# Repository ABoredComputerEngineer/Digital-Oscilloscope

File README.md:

# How to Run

* Requires `make`, `avr-gcc` and `avr-dude` for generating and flashing hex files
* Requires `numpy` and `matplotlib` for generating plots

### To Compile:
From project directory ( in the command line ), run:
```
make 
```
### To Flash:
* Make sure that the correct Arduino COM port is selected in the `Makefile`
From project directory ( in the command line ), run:
```
make flash
```

### To Generate Data for plot:
Once the program has been flashed and running, select the correct COM port for the USB-TTL
and run
```
python src/test.py > src/data
```
Hit `Ctrl-C` to stop execution once you think you have enough data and then run
```
python src/plot.py
```

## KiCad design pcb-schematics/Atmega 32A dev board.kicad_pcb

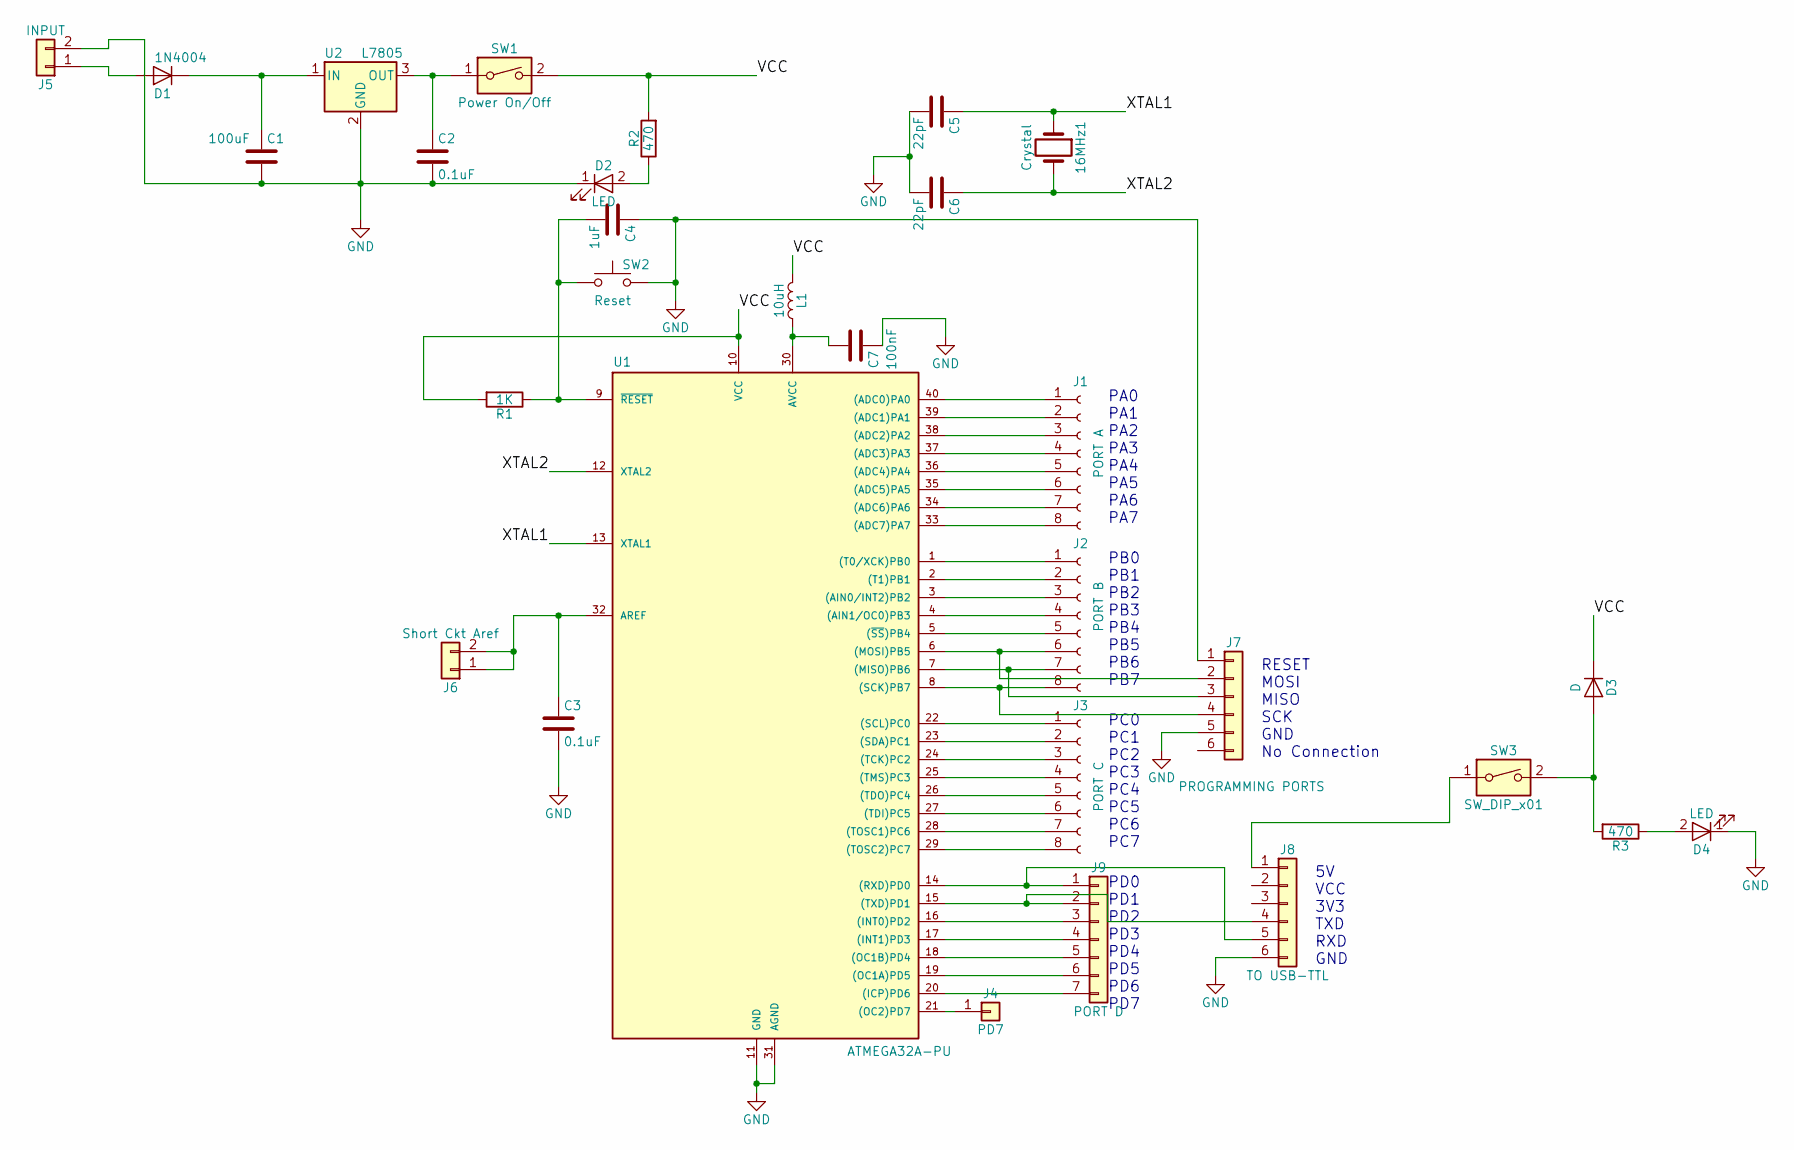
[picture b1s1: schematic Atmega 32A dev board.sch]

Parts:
16MHz1: Crystal
C1: 100uF; Capacitor_100uF
C2, C3: 0.1uF; Capacitor_Disc_Small
C4: 1uF; Capacitor_Disc_Small
C5, C6: 22pF; Capacitor_Disc_Medium
C7: 100nF; Capacitor_Disc_Small
D1: 1N4004; Diode_Medium
D2, D4: LED; LED_D3.0mm
D3: D; Diode_Medium
J1: PORT A; Socket_Strip_Straight_1x08_Pitch2.54mm
J2: PORT B; Socket_Strip_Straight_1x08_Pitch2.54mm
J3: PORT C; Socket_Strip_Straight_1x08_Pitch2.54mm
J4: PD7; Socket_Strip_Straight_1x01_Pitch2.54mm
J5: INPUT; Connector_Bornier_2
J6: Short Ckt Aref; Pin_Header_Straight_1x02_Pitch2.54mm
J7: PROGRAMMING PORTS; Socket_Strip_Straight_1x06_Pitch2.54mm
J8: TO USB-TTL; Socket_Strip_Straight_1x06_Pitch2.54mm
J9: PORT D; Socket_Strip_Straight_1x07_Pitch2.54mm
L1: 10uH; Resistor_small
R1: 1K; Resistor_small
R2, R3: 470; Resistor_small
SW1: Power On/Off; DIP_Switch
SW2: Reset; Push_Button
SW3: SW_DIP_x01; DIP_Switch
U1: ATMEGA32A-PU; DIP-40
U2: L7805; Voltage_Regulators

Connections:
/VCC: D3.1 (K), L1.2, R1.2, R2.2, SW1.2, U1.10 (VCC)
/XTAL1: 16MHz1.1, C5.1, U1.13 (XTAL1)
/XTAL2: 16MHz1.2, C6.1, U1.12 (XTAL2)
GND: C1.2, C2.2, C3.2, C4.1, C5.2, C6.2, C7.1, D2.1 (K), D4.1 (K), J5.2, J7.1, J7.5, J8.6, SW2.2, U1.11 (GND), U1.31 (AGND), U2.2 (GND)
unnamed: C1.1, D1.1 (K), U2.1 (IN)
unnamed: C2.1, SW1.1, U2.3 (OUT)
unnamed: C3.1, J6.1, J6.2, U1.32 (AREF)
unnamed: C4.2, R1.1, SW2.1, U1.9 (~RESET)
unnamed: C7.2, L1.1, U1.30 (AVCC)
unnamed: D1.2 (A), J5.1
unnamed: D2.2 (A), R2.1
unnamed: D3.2 (A), R3.2, SW3.2
unnamed: D4.2 (A), R3.1
unnamed: J1.1, U1.40 ((ADC0)PA0)
unnamed: J1.2, U1.39 ((ADC1)PA1)
unnamed: J1.3, U1.38 ((ADC2)PA2)
unnamed: J1.4, U1.37 ((ADC3)PA3)
unnamed: J1.5, U1.36 ((ADC4)PA4)
unnamed: J1.6, U1.35 ((ADC5)PA5)
unnamed: J1.7, U1.34 ((ADC6)PA6)
unnamed: J1.8, U1.33 ((ADC7)PA7)
unnamed: J2.1, U1.1 ((T0/XCK)PB0)
unnamed: J2.2, U1.2 ((T1)PB1)
unnamed: J2.3, U1.3 ((AIN0/INT2)PB2)
unnamed: J2.4, U1.4 ((AIN1/OC0)PB3)
unnamed: J2.5, U1.5 ((~SS~)PB4)
unnamed: J2.6, J7.2, U1.6 ((MOSI)PB5)
unnamed: J2.7, J7.3, U1.7 ((MISO)PB6)
unnamed: J2.8, J7.4, U1.8 ((SCK)PB7)
unnamed: J3.1, U1.22 ((SCL)PC0)
unnamed: J3.2, U1.23 ((SDA)PC1)
unnamed: J3.3, U1.24 ((TCK)PC2)
unnamed: J3.4, U1.25 ((TMS)PC3)
unnamed: J3.5, U1.26 ((TDO)PC4)
unnamed: J3.6, U1.27 ((TDI)PC5)
unnamed: J3.7, U1.28 ((TOSC1)PC6)
unnamed: J3.8, U1.29 ((TOSC2)PC7)
unnamed: J4.1, U1.21 ((OC2)PD7)
unnamed: J8.1, SW3.1
unnamed: J8.4, J9.2, U1.15 ((TXD)PD1)
unnamed: J8.5, J9.1, U1.14 ((RXD)PD0)
unnamed: J9.3, U1.16 ((INT0)PD2)
unnamed: J9.4, U1.17 ((INT1)PD3)
unnamed: J9.5, U1.18 ((OC1B)PD4)
unnamed: J9.6, U1.19 ((OC1A)PD5)
unnamed: J9.7, U1.20 ((ICP)PD6)

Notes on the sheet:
RESET MOSI MISO SCK GND No Connection
5V VCC 3V3 TXD RXD GND
PA0 PA1 PA2 PA3 PA4 PA5 PA6 PA7
PB0 PB1 PB2 PB3 PB4 PB5 PB6 PB7
PC0 PC1 PC2 PC3 PC4 PC5 PC6 PC7
PD0 PD1 PD2 PD3 PD4 PD5 PD6 PD7

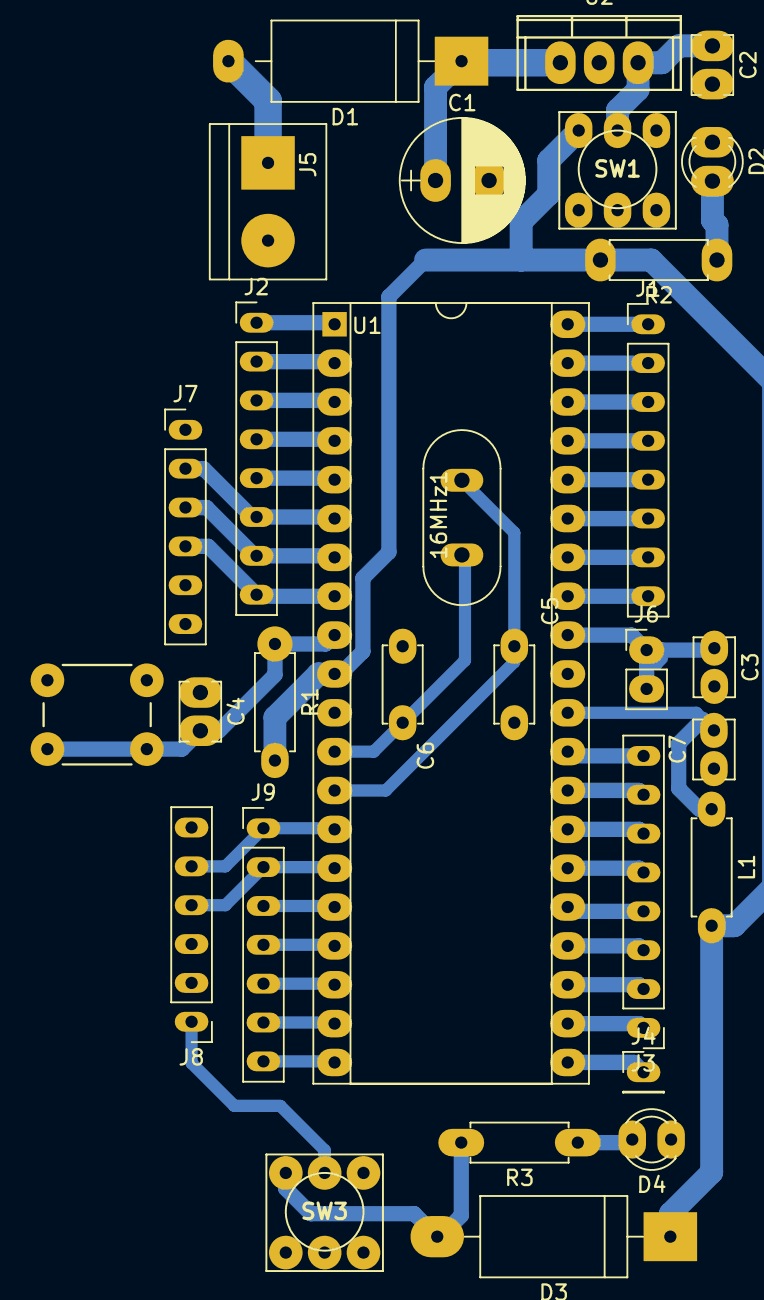
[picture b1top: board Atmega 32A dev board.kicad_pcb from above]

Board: 2 copper layers, 30 parts (0 on the bottom side), 46 nets.

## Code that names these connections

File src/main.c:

#define CLOCK_FREQUENCY
#define SANITY_CHECK 1

#ifndef F_CPU
  #define F_CPU 1000000
#endif

#include <avr/io.h>
#include <util/delay.h>
#include "setbaud.h"
#include <avr/interrupt.h>
#include <stdbool.h>

typedef unsigned int uint;
typedef uint16_t u16;
typedef uint8_t u8;
typedef uint32_t u32;

#define TRUE 1
#define FALSE 0
#define MAX_DATA_SIZE ( 3*600 )
static u8 data_to_send[MAX_DATA_SIZE]; 
#define BAUD_RATE 9600

#define WRITE_UBBRH( x ) ( UBBRH = ( x ) )
#define WRITE_USCRC( x ) ( USCRC = ( 1<<URSEL ) | ( x ) )

#define SET_BIT( src, bit ) ( ( src ) |= ( 1 << ( bit ) ) )
#define RESET_BIT( src, bit ) ( ( src ) &= ~(1 << ( bit ) ) )

#define ADC_CONVERSION_COMPLETE ( ADCSRA & ( 1 << ADIF ) )

#define ADC_ENABLE_BIT ADEN
enum ADC_Inputs {
  ADC_INPUT_0 = 0x0,
  ADC_INPUT_1 = 0x1,
  ADC_INPUT_7 = 0x7,
};

enum ADC_Refs {
  ADC_AREF = 0x0,
  ADC_AVCC = 0x1,
  ADC_INTERNAL = 0x3
};

enum ADC_Prescaler {
  ADC_PS_2 = 0x0,
  ADC_PS_4 = 0x2,
  ADC_PS_8 = 0x3,
  ADC_PS_16 = 0X4,
  ADC_PS_32 = 0x5,
  ADC_PS_64 = 0x6,
  ADC_PS_128 = 0x7
};

enum Timer_Prescaler {
  TIMER_PS_NONE = 0x0,
  TIMER_PS_1 = 0x1,
  TIMER_PS_8 = 0x2,
  TIMER_PS_64 = 0x3,
  TIMER_PS_256= 0x4,
  TIMER_PS_1024 = 0x5,
  TIMER_PS_EXTERNAL_FALL = 0x6,
  TIMER_PS_EXTERNAL_RISE = 0x7,
};

enum Timer2_Prescaler {
  TIMER2_PS_NONE = 0x0,
  TIMER2_PS_1 = 0x1,
  TIMER2_PS_8 = 0x2,
  TIMER2_PS_32 = 0x3,
  TIMER2_PS_64 = 0x4,
  TIMER2_PS_128 = 0x5,
  TIMER2_PS_256 = 0x6,
  TIMER2_PS_1024 = 0x7,
};

typedef enum Program_State{
  STATE_INACTIVE,
  STATE_ADC_CONVERSION_FAST,
  STATE_ADC_CONVERSION_SLOW
} Program_State;

volatile Program_State Global_State;
volatile u8 End_Of_Conversion = FALSE;

static u8 Timer_Duration[] = {
  0x4c, 0x4a, // 5sec with 1MHz, PS =256 
  0x98, 0x95, // 10sec with 1MHz, PS =256 
};

void USART_init( u16 baud ){
 // Set the baud rate
  //UBRRH = 0x01;
  //UBRRL = 0x04;
  setBaud( 9600, 1.0e6 );
  // Enable reciever and transmitter
  UCSRB = ( 1 << RXEN ) | ( 1 << TXEN );

  // Set the frame format: 8-bit data ( USCZ0 ), 1 stop bits
  // Asynchronous operation
  //UCSRC = ( 1 << URSEL ) | ( 0 << USBS ) | ( 0x3 << UCSZ0 );

  // 8-bit per frame with no parity, 1 stop bit
  UCSRC = ( 1 << URSEL ) | ( 0 << USBS ) | ( 0x3 << UCSZ0 );

}


void USART_Transmit( u8 data ){
  // Wait until all the remaining data has been transmitted
  while ( !(UCSRA&(1<<UDRE) ) );

  // Send the data by storing it in UDR Register
  UDR = data;
}

void USART_Transmit_Buffer( u8 *buff, u8 len ){
  for ( u8 i = 0; i < len; i++ ){
    USART_Transmit( *( buff + i )  ); 
  }
}


u8 USART_Receive( void ){
  // Wait for data to be received fully
  PORTD |= ( 1 << PD6 );
  while ( !( UCSRA & ( 1 << RXC ) ) );
  PORTD &= ~( 1 << PD6 );
  return UDR; 
}

void ADC_Init( u8 prescaler, u8 left_adjust ){
  // Enable the ADC
  ADCSRA |= ( ( 1 << ADEN ) | ( prescaler & 0x7 ) );
  ADMUX |= ( (left_adjust<<ADLAR) | ( ADC_AVCC << REFS0 ) );

}

void ADC_Disable( ){
  RESET_BIT( ADCSRA, ADC_ENABLE_BIT );
}


u16 ADC_GetData( u8 input_pin ){
#if SANITY_CHECK
  ADMUX |= ( input_pin & 0x1f );
#else
  ADMUX |= input_pin
#endif

  SET_BIT( ADCSRA, ADSC );

  // TODO: Maybe not block and use interrupts 
  // block until the conversion completes
  while ( !ADC_CONVERSION_COMPLETE );

  // This step is mandatory
  u8 lower = ADCL;
#if SANITY_CHECK
  u16 higher = ADCH;
  u16 result = ( ( higher & 0x3f ) << 8 ) |  lower;
  return result;
#else
  return ( ( (u16)ADCH & 0x3f ) << 8 ) | lower;
#endif
}

void Timer1_Init( u8 ps, u8 high, u8 low ){
  // toggle OCA1 on compare match
  // CTC Mode, Sets WGM 11 and WGM 10
  TCCR1A = ( 0x1 << COM1A0 );
  TCCR1B |= ( 0x1 << WGM12 ); // Sets  WGM13 and WGM12
  TCCR1B |= ps; 
  TIMSK |= ( 0x1 << OCIE1A );
  // The order is important!!
  OCR1AH = high;
  OCR1AL = low;
}

#if 0
void Timer2_Init( u8 ps ){
  // Normal Mode
  TCCR2 |= ( ps & 0x7 );
}
#endif


ISR(TIMER1_COMPA_vect){
  PORTD |= (1<<PD6);
  Global_State = STATE_INACTIVE;
  End_Of_Conversion = TRUE;
}


static inline void Timer1_Reset( void ){
//  SFIOR &= ~(1<<PSR10); // Reset the timer
  TCNT1 ^= TCNT1;
}

static inline void Timer2_Reset( void ){
  SFIOR &= ~(1<<PSR2);
}

void ADC_Convert_Fast( void ){
  RESET_BIT( PORTD, PD6 );
  ADC_Init(ADC_PS_4,1);
  u8 time;
  u8 *start = data_to_send;
  u8 *end = data_to_send + MAX_DATA_SIZE;
  Timer1_Reset();
  Timer2_Reset();
  while( start < end ){ 
    time = TCNT2;
    TCNT2 = 0;
    ADMUX |= ( ADC_INPUT_0  );
    SET_BIT( ADCSRA, ADSC );
    *start = time; start++;
    while ( !ADC_CONVERSION_COMPLETE );
    *start = ADCH; start++;
    ADMUX &= ~(ADC_INPUT_0 ); 
    ADMUX |= ( ADC_INPUT_7  );
    SET_BIT( ADCSRA, ADSC );
    while ( !ADC_CONVERSION_COMPLETE );
    *start = ADCH; start++;
    ADMUX &= ~( ADC_INPUT_7 );
   }
  PORTD |= (1<<PD6);
  Global_State = STATE_INACTIVE;
  for ( u8 *s = data_to_send; s < end; s++ ){ 
    USART_Transmit( *s );
  }
}

void ADC_Convert_Slow( void ){
  u8 time;
  RESET_BIT( PORTD, PD6 );
  ADC_Init(ADC_PS_4, 0);
  RESET_BIT(ADMUX,ADLAR);
  Timer1_Reset();
  Timer2_Reset();
  End_Of_Conversion = FALSE;
  while ( End_Of_Conversion == FALSE ){ 
          ADMUX |= ( ADC_INPUT_0  );
          SET_BIT( ADCSRA, ADSC );
          time = TCNT2;
          TCNT2 = 0;
          while ( !ADC_CONVERSION_COMPLETE );
          data_to_send[0] = time;
          data_to_send[1] = ADCL;
          data_to_send[2] = ADCH  & 0x3;
          ADMUX &= ~(ADC_INPUT_0 );

          ADMUX |= ( ADC_INPUT_7  );
          SET_BIT( ADCSRA, ADSC );
          while ( !ADC_CONVERSION_COMPLETE );
          data_to_send[3] = time;
          data_to_send[4] = ADCL;
          data_to_send[5] = ADCH  & 0x3;

          USART_Transmit_Buffer( data_to_send, 6 );
          ADMUX &= ~( ADC_INPUT_7 );
   }
   cli();
   for ( u8 i = 0; i < 6 ; i++ ){
     USART_Transmit( 1 << 0x7 );
   }
   End_Of_Conversion = FALSE;
}

int main(void){
  cli();
#if 1
  DDRD |= (1<<PD7)|(1<<PD6)|(1<<PD5)|(1<<PD4) ;
  USART_init( 6 );  
//  ADC_Init( ADC_PS_4 ); 
  Global_State = STATE_INACTIVE;
  for ( ; ; ){
      ADC_Disable();
      SET_BIT( PORTD, PD6 ); 
      RESET_BIT( PORTD, PD4 );
      u8 input1 = USART_Receive();
      u8 input2 = USART_Receive();
       if ( input1 ){
        Global_State = STATE_ADC_CONVERSION_FAST;
        TCCR2 =  TIMER2_PS_1 & 0x7;
        ADC_Convert_Fast();
      } else {
        Global_State = STATE_ADC_CONVERSION_SLOW;
        sei();
        TCCR2 =  TIMER2_PS_128 & 0x7;
        if ( input2 == 0x0 ) {
          Timer1_Init( TIMER_PS_256,
              Timer_Duration[0],
              Timer_Duration[1] );
        } else {
          Timer1_Init( TIMER_PS_256,
              Timer_Duration[2],
              Timer_Duration[3] );
        }
        ADC_Convert_Slow();
      }

  }
#else 
 while ( 1 ){

 }
 #endif
  return 0;
}

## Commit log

2019-12-31 Added few more links
2020-01-01 Some more links and docs
2020-01-04 Added simple conditioning circuit
2020-01-18 PCB design for Atmega 32 Dev Board
2020-01-19 Added avr code and some basic plotting ability
2020-01-19 Added output figure
2020-01-19 cleaned up directories
2020-01-22 Added timers
2020-01-22 Panick commit
2020-01-23 added button to plot"
2020-01-24 Added scrolling plot
2020-01-24 Almost Final
2020-01-30 Done in Department
2020-01-31 Added hf and lf modes
2020-01-31 Fixed bug with lf mode
2020-01-31 Fixed atmega code for lf left adjust
2020-01-31 Fixed prescaler
2020-01-31 Almost final commit
